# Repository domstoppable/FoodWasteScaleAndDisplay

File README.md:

# Food waste scale and display

## Firmware
Build and upload with Arduino

## Display app
### Building
* Install [`react-native`](https://facebook.github.io/react-native/docs/getting-started)
* Install the Android SDK
* Make sure the `ANDROID_HOME` environment variable is set appropriately
* Build and test the app
	```bash
	cd ScaleDisplayApp
	npm install
	npm run-android
	```
* Make a native release build and install it ([signing key required](https://facebook.github.io/react-native/docs/signed-apk-android))
	```bash
	cd ScaleDisplayApp/android
	./gradlew assembleRelease
	adb install build/outputs/apk/release/app-release.apk
	cd ..
	```

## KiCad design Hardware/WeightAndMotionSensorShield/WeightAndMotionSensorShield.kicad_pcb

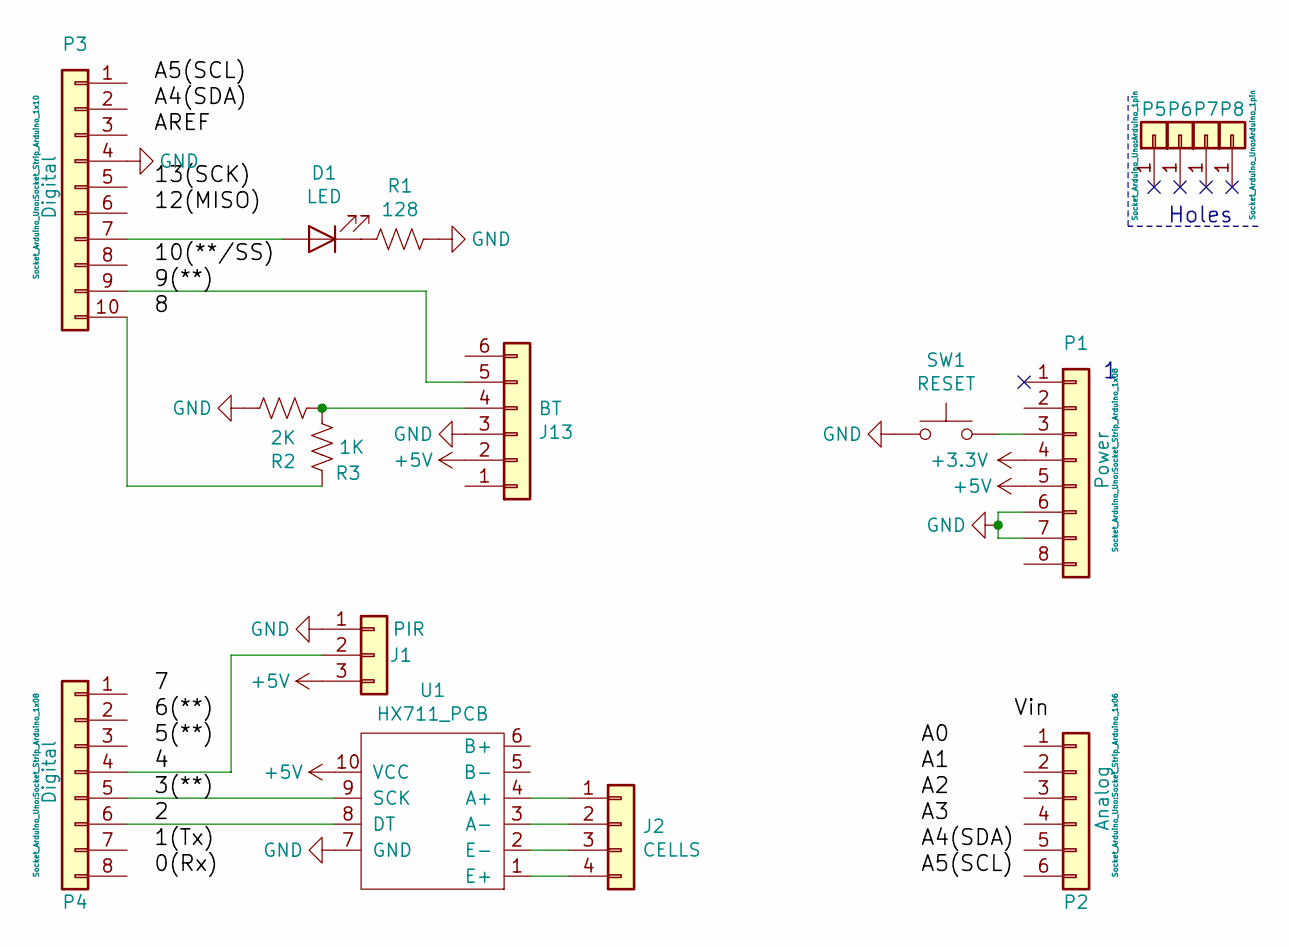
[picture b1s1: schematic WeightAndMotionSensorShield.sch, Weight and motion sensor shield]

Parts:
D1: LED; LED_D5.0mm
J1: PIR; PinSocket_1x03_P2.54mm_Horizontal
J2: CELLS; PinSocket_1x04_P2.54mm_Horizontal
J13: BT; PinHeader_1x06_P2.54mm_Vertical
P1: Power; Socket_Strip_Arduino_1x08
P2: Analog; Socket_Strip_Arduino_1x06
P3: Digital; Socket_Strip_Arduino_1x10
P4: Digital; Socket_Strip_Arduino_1x08
P5, P6, P7, P8: CONN_01X01; Arduino_1pin
R1: 128; R_Axial_DIN0207_L6.3mm_D2.5mm_P10.16mm_Horizontal
R2: 2K; R_Axial_DIN0207_L6.3mm_D2.5mm_P10.16mm_Horizontal
R3: 1K; R_Axial_DIN0207_L6.3mm_D2.5mm_P10.16mm_Horizontal
SW1: RESET; SW_PUSH_6mm
U1: HX711_PCB

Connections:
+3V3: P1.4
+5V: J1.3, J13.2, P1.5, U1.10 (VCC); also elsewhere on the board
/2: P4.6, U1.8 (DT)
/3(**): P4.5, U1.9 (SCK)
/4: J1.2, P4.4; also elsewhere on the board
/9(**): J13.5, P3.9
GND: J1.1, J13.3, P1.6, P1.7, P3.4, R1.1, R2.1, SW1.1, U1.7 (GND); also elsewhere on the board
unnamed: D1.1 (K), R1.2
unnamed: D1.2 (A), P3.7
unnamed: J2.1, U1.4 (A+)
unnamed: J2.2, U1.3 (A-)
unnamed: J2.3, U1.2 (E-)
unnamed: J2.4, U1.1 (E+)
unnamed: J13.4, R2.2, R3.2
unnamed: P1.3, SW1.2
unnamed: P3.10, R3.1

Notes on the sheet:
Holes

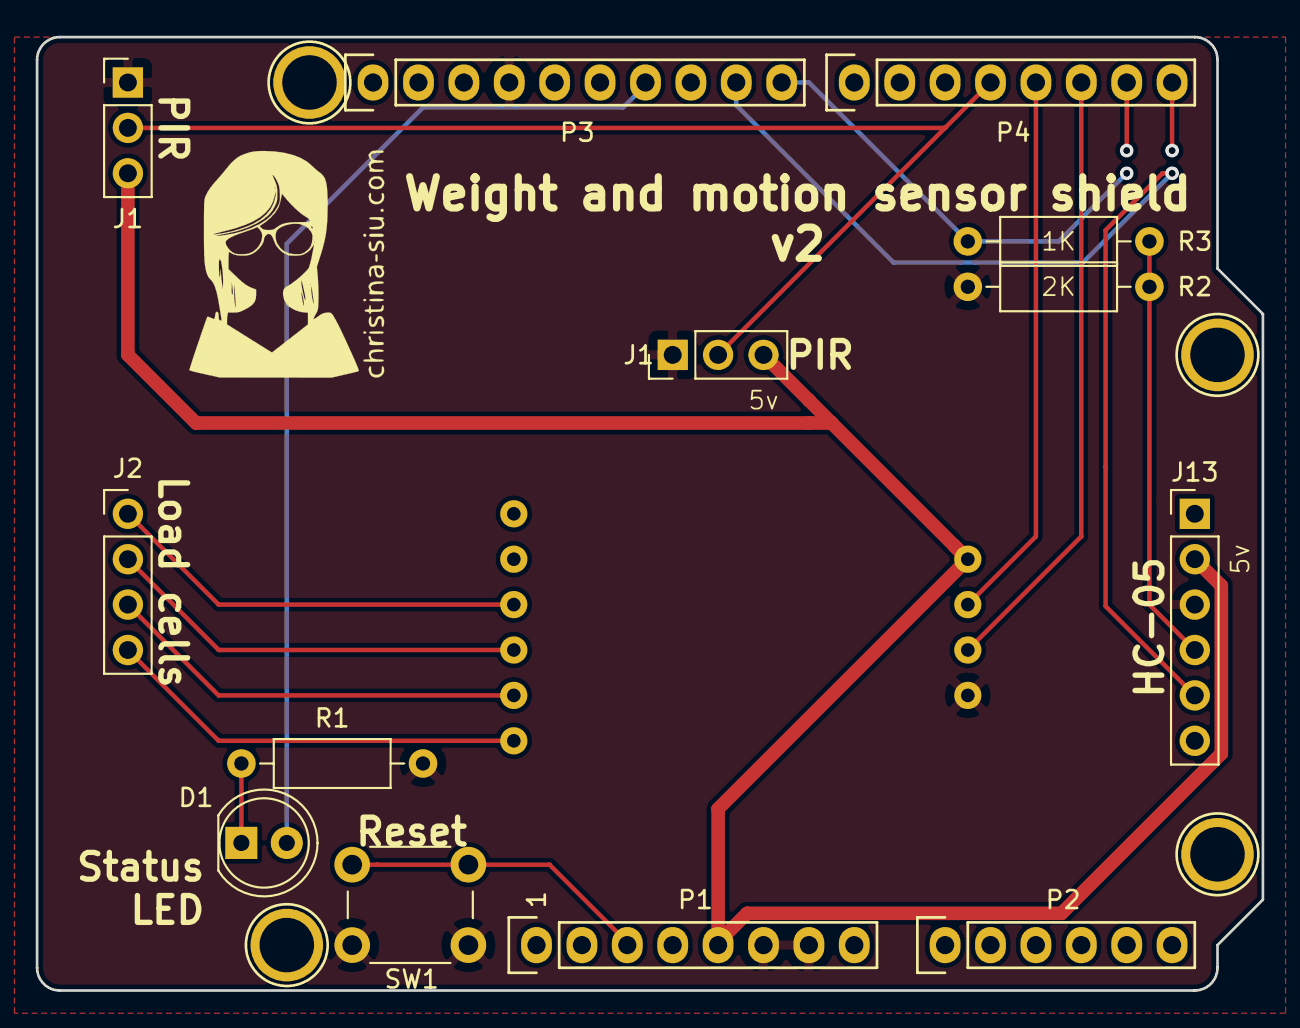
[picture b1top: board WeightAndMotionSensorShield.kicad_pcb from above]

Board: 2 copper layers, 68.6 x 53.3 mm, 18 parts (1 on the bottom side), 15 nets.

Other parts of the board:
J1#2: PIR; PinHeader_1x03_P2.54mm_Vertical

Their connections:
+5V: J1#2.3; also elsewhere on the board
/4: J1#2.2; also elsewhere on the board
GND: J1#2.1; also elsewhere on the board

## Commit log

2019-07-16 Add PCB design for Arduino shield
2019-07-23 Adds LED, reset button, 2nd PIR header
2019-08-18 PCB v1.1 and 2 changes
2019-09-23 Split AppContainer into individual component files
2019-10-10 Added functioning Baseline and Ambient conditions. Need pictures and colors for the Ambient and Metaphorical conditions. Data can be logged locally via RNFetchBlob Operator button located in the bott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
    TODO: Google Sheets and Weight detector (to determine logging)
2019-12-29 Bump handlebars from 4.1.2 to 4.5.3 in /DisplayApp
    Bumps [handlebars](https://github.com/wycats/handlebars.js) from 4.1.2 to 4.5.3.
    - [Release notes](https://github.com/wycats/handlebars.js/releases)
    - [Changelog](https://github.com/wycats/handlebars.js/blob/master/release-notes.md)
    - [Commits](https://github.com/wycats/handlebars.js/compare/v4.1.2...v4.5.3)
2020-01-10 More functions
2020-01-10 Added landscape mode and specific things to install easier
2020-01-11 Functional version of bluetooth serial with react-native-ble-plx rn-fetch-blob removed from this version. Does not work with dex installation in AndroidX react-native-fetch-blob temporarily removed. 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
2020-01-11 Adding package.json
2020-01-11 Added image in metaphoric
2020-01-12 Sort of functioning for BLE devices, but the HC-05 unit ordered is not BLE
2020-01-12 Working bluetooth data reader. Need to do a lot more to stabilize things
    1) Bluetooth picker
    2) Auto-connect
    3) Properly disconnect bluetooth device so you do not need to completely disconnect bluetooth from power
2020-01-13 Added bluetooth stabilization Added midnight function Added weight change detection
2020-01-13 Added arduino updated script so that we can send command to tare
2020-01-13 Added calibration menu Added ToastAndroid instead of console.warns everywhere for some crisper tastes Need to figure out weightchange algorithm. Can detect changes, but need to think of how to contin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
2020-01-20 Add header for HC-05 module
2020-03-07 Fixed calibrations to save values from configCal file
2020-03-14 Update pins for new board + add LED pin
2020-03-14 Implement softserial + serial debug
2020-03-16 Bump acorn from 5.7.3 to 5.7.4 in /DisplayApp
    Bumps [acorn](https://github.com/acornjs/acorn) from 5.7.3 to 5.7.4.
    - [Release notes](https://github.com/acornjs/acorn/releases)
    - [Commits](https://github.com/acornjs/acorn/compare/5.7.3...5.7.4)
2020-04-19 Updated ScaleFirmware for calibrations
2020-07-17 Bump lodash from 4.17.11 to 4.17.19 in /DisplayApp
    Bumps [lodash](https://github.com/lodash/lodash) from 4.17.11 to 4.17.19.
    - [Release notes](https://github.com/lodash/lodash/releases)
    - [Commits](https://github.com/lodash/lodash/compare/4.17.11...4.17.19)
2020-09-06 Bump handlebars from 4.1.2 to 4.7.6 in /DisplayApp
    Bumps [handlebars](https://github.com/wycats/handlebars.js) from 4.1.2 to 4.7.6.
    - [Release notes](https://github.com/wycats/handlebars.js/releases)
    - [Changelog](https://github.com/handlebars-lang/handlebars.js/blob/master/release-notes.md)
    - [Commits](https://github.com/wycats/handlebars.js/compare/v4.1.2...v4.7.6)
2021-03-30 Bump y18n from 3.2.1 to 3.2.2 in /DisplayApp
    Bumps [y18n](https://github.com/yargs/y18n) from 3.2.1 to 3.2.2.
    - [Release notes](https://github.com/yargs/y18n/releases)
    - [Changelog](https://github.com/yargs/y18n/blob/master/CHANGELOG.md)
    - [Commits](https://github.com/yargs/y18n/commits)
2021-04-15 More final version. Added ambient
2021-04-15 Cleaned up buttons
2021-05-07 Bump ua-parser-js from 0.7.19 to 0.7.28 in /DisplayApp
    Bumps [ua-parser-js](https://github.com/faisalman/ua-parser-js) from 0.7.19 to 0.7.28.
    - [Release notes](https://github.com/faisalman/ua-parser-js/releases)
    - [Commits](https://github.com/faisalman/ua-parser-js/compare/0.7.19...0.7.28)
2021-05-08 Bump handlebars from 4.1.2 to 4.7.7 in /DisplayApp
    Bumps [handlebars](https://github.com/wycats/handlebars.js) from 4.1.2 to 4.7.7.
    - [Release notes](https://github.com/wycats/handlebars.js/releases)
    - [Changelog](https://github.com/handlebars-lang/handlebars.js/blob/master/release-notes.md)
    - [Commits](https://github.com/wycats/handlebars.js/compare/v4.1.2...v4.7.7)
2021-05-09 Bump lodash from 4.17.11 to 4.17.21 in /DisplayApp
    Bumps [lodash](https://github.com/lodash/lodash) from 4.17.11 to 4.17.21.
    - [Release notes](https://github.com/lodash/lodash/releases)
    - [Commits](https://github.com/lodash/lodash/compare/4.17.11...4.17.21)
2021-05-10 Bump hosted-git-info from 2.7.1 to 2.8.9 in /DisplayApp
    Bumps [hosted-git-info](https://github.com/npm/hosted-git-info) from 2.7.1 to 2.8.9.
    - [Release notes](https://github.com/npm/hosted-git-info/releases)
    - [Changelog](https://github.com/npm/hosted-git-info/blob/v2.8.9/CHANGELOG.md)
    - [Commits](https://github.com/npm/hosted-git-info/compare/v2.7.1...v2.8.9)
2021-05-15 near final build
2021-05-15 final build
2021-08-11 Bump path-parse from 1.0.6 to 1.0.7 in /DisplayApp
    Bumps [path-parse](https://github.com/jbgutierrez/path-parse) from 1.0.6 to 1.0.7.
    - [Release notes](https://github.com/jbgutierrez/path-parse/releases)
    - [Commits](https://github.com/jbgutierrez/path-parse/commits/v1.0.7)
    ---
    updated-dependencies:
    - dependency-name: path-parse
2021-09-21 Bump tmpl from 1.0.4 to 1.0.5 in /DisplayApp
    Bumps [tmpl](https://github.com/daaku/nodejs-tmpl) from 1.0.4 to 1.0.5.
    - [Release notes](https://github.com/daaku/nodejs-tmpl/releases)
    - [Commits](https://github.com/daaku/nodejs-tmpl/commits/v1.0.5)
    ---
    updated-dependencies:
    - dependency-name: tmpl
2021-11-15 Bump react-native-webview from 7.4.1 to 11.0.0 in /DisplayApp
    Bumps [react-native-webview](https://github.com/react-native-webview/react-native-webview) from 7.4.1 to 11.0.0.
    - [Release notes](https://github.com/react-native-webview/react-native-webview/releases)
    - [Changelog](https://github.com/react-native-webview/react-native-webview/blob/master/.releaserc)
    - [Commits](https://github.com/react-native-webview/react-native-webview/compare/v7.4.1...v11.0.0)
    ---
    updated-dependencies:
2021-11-15 Bump https-proxy-agent from 2.2.2 to 2.2.4 in /DisplayApp
    Bumps [https-proxy-agent](https://github.com/TooTallNate/node-https-proxy-agent) from 2.2.2 to 2.2.4.
    - [Release notes](https://github.com/TooTallNate/node-https-proxy-agent/releases)
    - [Commits](https://github.com/TooTallNate/node-https-proxy-agent/compare/2.2.2...2.2.4)
    ---
    updated-dependencies:
    - dependency-name: https-proxy-agent
2021-11-15 Bump react-native from 0.59.5 to 0.62.3 in /DisplayApp
    Bumps [react-native](https://github.com/facebook/react-native) from 0.59.5 to 0.62.3.
    - [Release notes](https://github.com/facebook/react-native/releases)
    - [Changelog](https://github.com/facebook/react-native/blob/main/Releases.md)
    - [Commits](https://github.com/facebook/react-native/compare/v0.59.5...v0.62.3)
    ---
    updated-dependencies:
2022-02-12 Bump ajv from 6.10.2 to 6.12.6 in /DisplayApp
    Bumps [ajv](https://github.com/ajv-validator/ajv) from 6.10.2 to 6.12.6.
    - [Release notes](https://github.com/ajv-validator/ajv/releases)
    - [Commits](https://github.com/ajv-validator/ajv/compare/v6.10.2...v6.12.6)
    ---
    updated-dependencies:
    - dependency-name: ajv
2022-03-01 Bump plist from 3.0.1 to 3.0.4 in /DisplayApp
    Bumps [plist](https://github.com/TooTallNate/node-plist) from 3.0.1 to 3.0.4.
    - [Release notes](https://github.com/TooTallNate/node-plist/releases)
    - [Changelog](https://github.com/TooTallNate/plist.js/blob/master/History.md)
    - [Commits](https://github.com/TooTallNate/node-plist/commits)
    ---
    updated-dependencies:
2022-04-28 Bump async from 2.6.2 to 2.6.4 in /DisplayApp
    Bumps [async](https://github.com/caolan/async) from 2.6.2 to 2.6.4.
    - [Release notes](https://github.com/caolan/async/releases)
    - [Changelog](https://github.com/caolan/async/blob/v2.6.4/CHANGELOG.md)
    - [Commits](https://github.com/caolan/async/compare/v2.6.2...v2.6.4)
    ---
    updated-dependencies:
2022-06-02 Bump simple-plist from 1.0.0 to 1.3.1 in /DisplayApp
    Bumps [simple-plist](https://github.com/wollardj/simple-plist) from 1.0.0 to 1.3.1.
    - [Release notes](https://github.com/wollardj/simple-plist/releases)
    - [Commits](https://github.com/wollardj/simple-plist/compare/v1.0.0...v1.3.1)
    ---
    updated-dependencies:
    - dependency-name: simple-plist
2022-10-12 Bump xmldom and plist in /DisplayApp
    Removes [xmldom](https://github.com/xmldom/xmldom). It's no longer used after updating ancestor dependency [plist](https://github.com/TooTallNate/node-plist). These dependencies need to be updated to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
    Removes `xmldom`
    Updates `plist` from 3.0.1 to 3.0.6
    - [Release notes](https://github.com/TooTallNate/node-plist/releases)
    - [Changelog](https://github.com/TooTallNate/plist.js/blob/master/History.md)
    - [Commits](https://github.com/TooTallNate/node-plist/commits)
2022-12-04 Bump decode-uri-component from 0.2.0 to 0.2.2 in /DisplayApp
    Bumps [decode-uri-component](https://github.com/SamVerschueren/decode-uri-component) from 0.2.0 to 0.2.2.
    - [Release notes](https://github.com/SamVerschueren/decode-uri-component/releases)
    - [Commits](https://github.com/SamVerschueren/decode-uri-component/compare/v0.2.0...v0.2.2)
    ---
    updated-dependencies:
    - dependency-name: decode-uri-component
2022-12-06 Bump qs from 6.5.2 to 6.5.3 in /DisplayApp
    Bumps [qs](https://github.com/ljharb/qs) from 6.5.2 to 6.5.3.
    - [Release notes](https://github.com/ljharb/qs/releases)
    - [Changelog](https://github.com/ljharb/qs/blob/main/CHANGELOG.md)
    - [Commits](https://github.com/ljharb/qs/compare/v6.5.2...v6.5.3)
    ---
    updated-dependencies:
2022-12-14 Bump express from 4.17.1 to 4.17.3 in /DisplayApp
    Bumps [express](https://github.com/expressjs/express) from 4.17.1 to 4.17.3.
    - [Release notes](https://github.com/expressjs/express/releases)
    - [Changelog](https://github.com/expressjs/express/blob/master/History.md)
    - [Commits](https://github.com/expressjs/express/compare/4.17.1...4.17.3)
    ---
    updated-dependencies:
2023-01-04 Bump json5 from 2.1.0 to 2.2.3 in /DisplayApp
    Bumps [json5](https://github.com/json5/json5) from 2.1.0 to 2.2.3.
    - [Release notes](https://github.com/json5/json5/releases)
    - [Changelog](https://github.com/json5/json5/blob/main/CHANGELOG.md)
    - [Commits](https://github.com/json5/json5/compare/v2.1.0...v2.2.3)
    ---
    updated-dependencies:

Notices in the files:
Hardware/WeightAndMotionSensorShield/WeightAndMotionSensorShield.kicad_pcb:
License: CC BY 4.0
Hardware/WeightAndMotionSensorShield/WeightAndMotionSensorShield.sch:
creativecommons.org/licenses/by/4.0
